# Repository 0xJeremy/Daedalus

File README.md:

# Daedalus Motor Controller

### Board Layout

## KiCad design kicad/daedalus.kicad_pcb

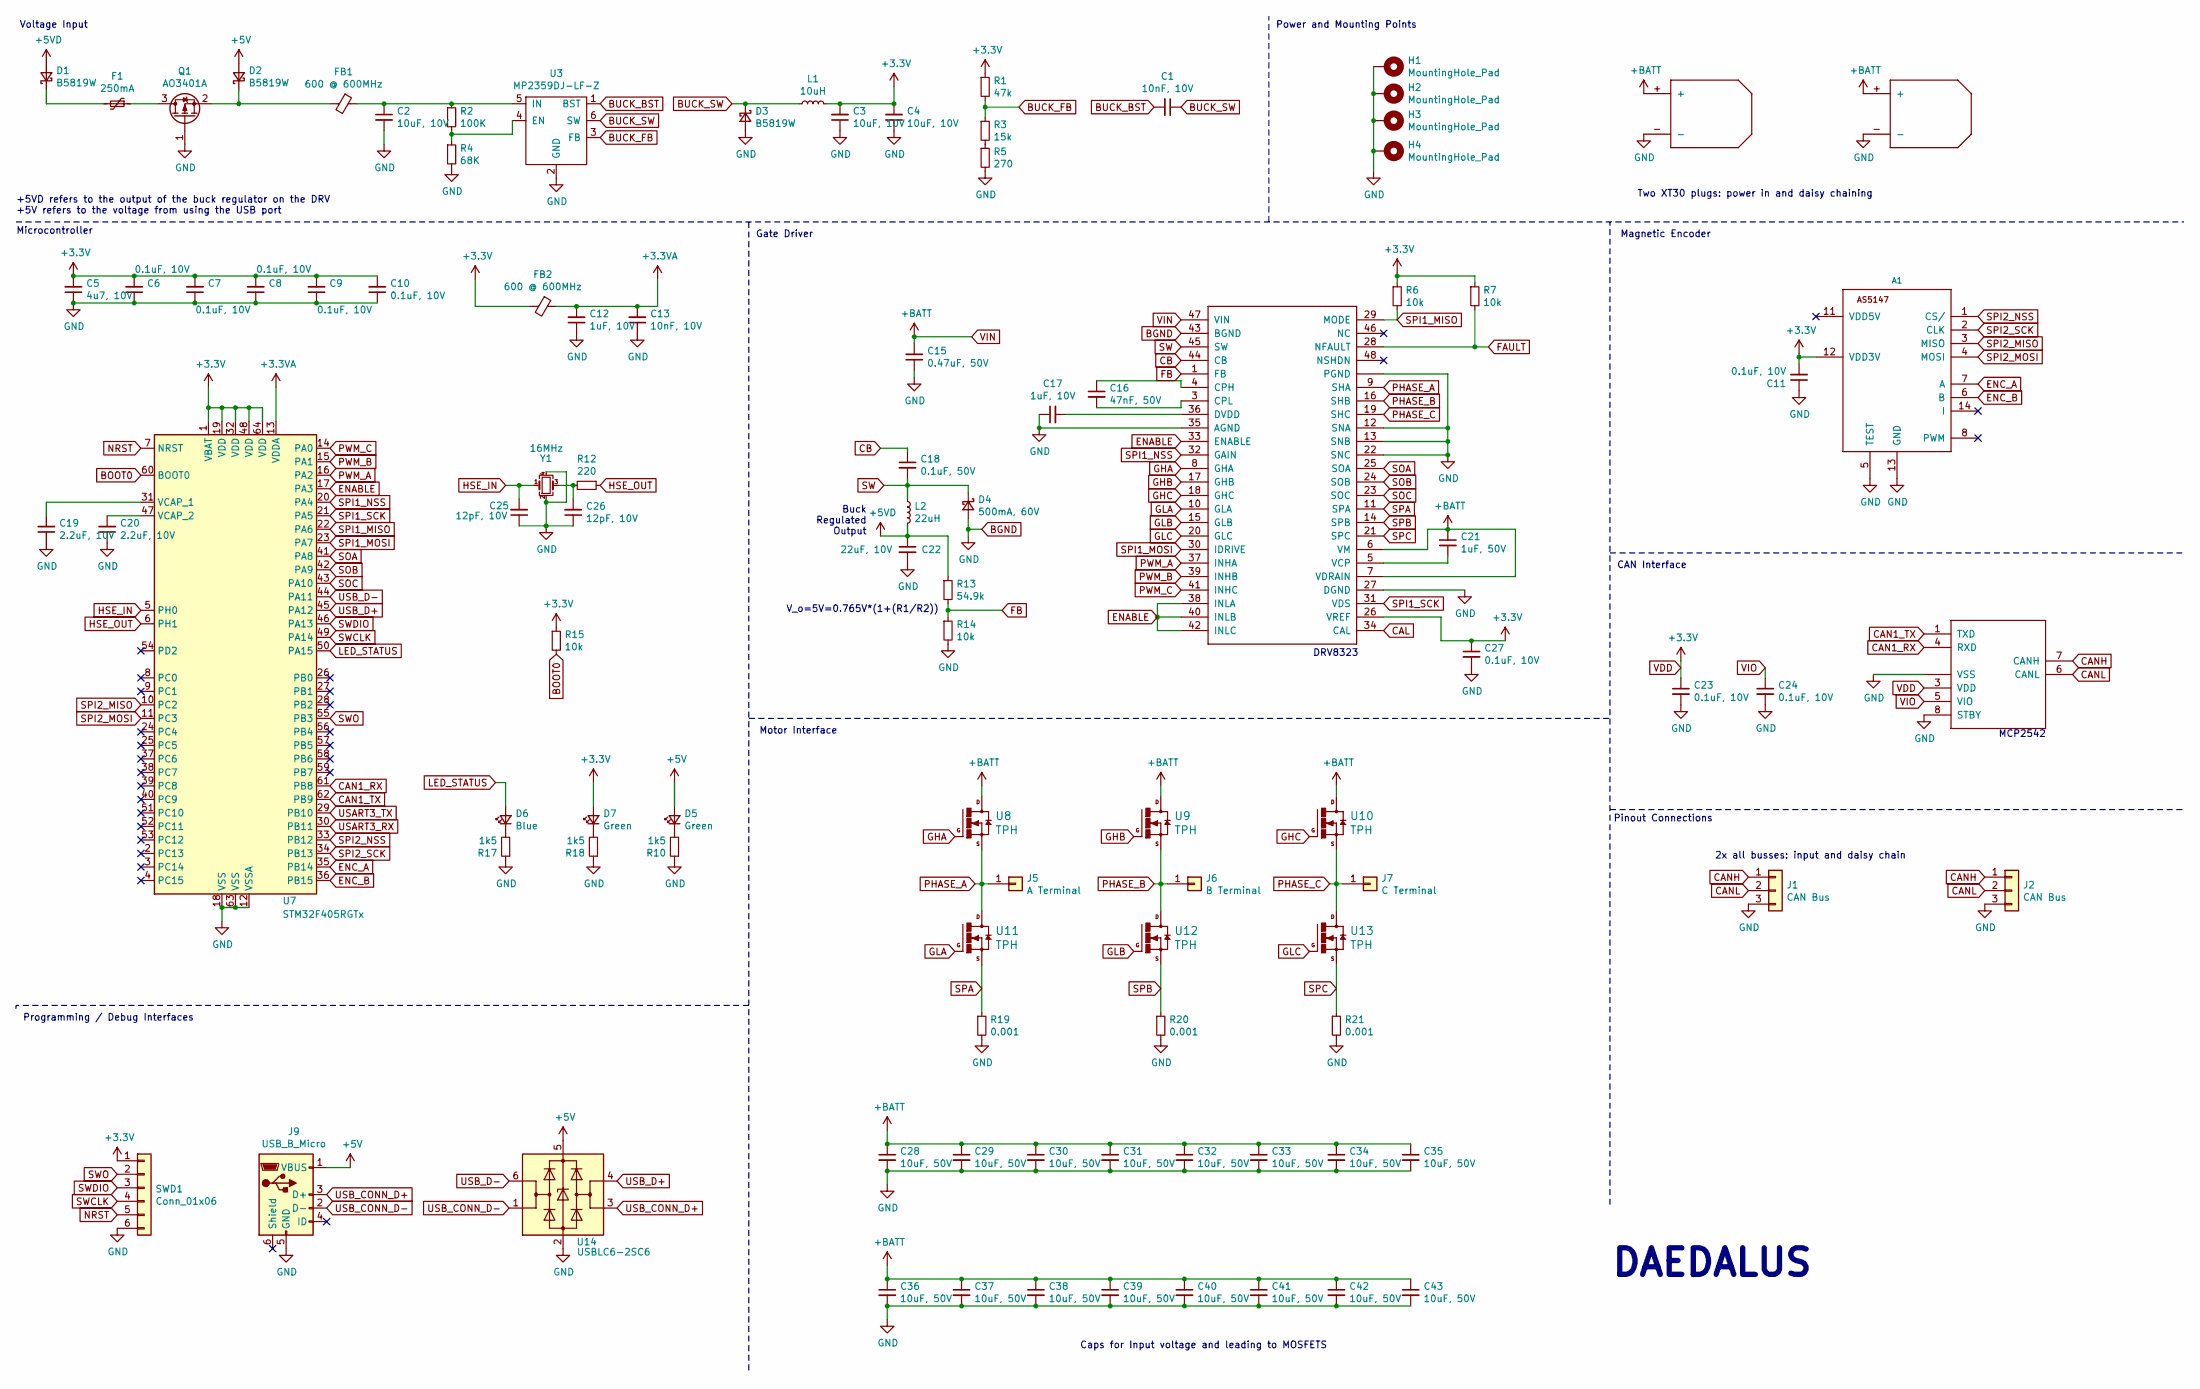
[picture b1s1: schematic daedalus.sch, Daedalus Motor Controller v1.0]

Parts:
A1: AS5147; TSSOP14_as5147
C1: 10nF, 10V; C_0402_1005Metric
C2, C3, C4: 10uF, 10V; C_0402_1005Metric
C5: 4u7, 10V; C_0402_1005Metric; LCSC Part # C23733
C6, C7, C8, C9, C10: 0.1uF, 10V; C_0402_1005Metric; LCSC Part # C1525
C11, C23, C24, C27: 0.1uF, 10V; C_0402_1005Metric
C12: 1uF, 10V; C_0402_1005Metric; LCSC Part # C1525
C13: 10nF, 10V; C_0402_1005Metric; LCSC Part # C1523
C15: 0.47uF, 50V; C_0402_1005Metric
C16: 47nF, 50V; C_0402_1005Metric
C17: 1uF, 10V; C_0402_1005Metric
C18: 0.1uF, 50V; C_0402_1005Metric
C19, C20: 2.2uF, 10V; C_0603_1608Metric; LCSC Part # C23630
C21: 1uF, 50V; C_0402_1005Metric
C22: 22uF, 10V; C_0402_1005Metric
C25, C26: 12pF, 10V; C_0402_1005Metric; LCSC Part # C1547
C28, C29, C30, C31, C32, C33, C34, C35, C36, C37, C38, C39, C40, C41, C42, C43: 10uF, 50V; C_0805_2012Metric
D1, D2, D3: B5819W; D_SOD-123
D4: 500mA, 60V; D_SOD-123
D5, D7: Green; LED_0603_1608Metric; LCSC Part # C2286
D6: Blue; LED_0603_1608Metric; LCSC Part # C2286
F1: 250mA; Fuse_0603_1608Metric
FB1: 600 @ 600MHz; L_0805_2012Metric
FB2: 600 @ 600MHz; L_0805_2012Metric; LCSC Part # C1015
H1, H2, H3, H4: MountingHole_Pad; MountingHole_2.7mm_M2.5_DIN965_Pad
J1, J2: CAN Bus; JST_PH_S3B-PH-SM4-TB_1x03-1MP_P2.00mm_Horizontal
J5: A Terminal; 18_AWG_PAD
J6: B Terminal; 18_AWG_PAD
J7: C Terminal; 18_AWG_PAD
J9: USB_B_Micro; USB_Micro-AB_Molex_47590-0001
L1: 10uH; L_0603_1608Metric
L2: 22uH; L_0603_1608Metric
Q1: AO3401A; SOT-23
R1: 47k; R_0402_1005Metric
R2: 100K; R_0402_1005Metric
R3: 15k; R_0402_1005Metric
R4: 68K; R_0402_1005Metric
R5: 270; R_0402_1005Metric
R6, R7, R14: 10k; R_0402_1005Metric
R10, R17, R18: 1k5; R_0402_1005Metric; LCSC Part # C25867
R12: 220; R_0402_1005Metric; LCSC Part # C22962
R13: 54.9k; R_0402_1005Metric
R15: 10k; R_0402_1005Metric; LCSC Part # C25744
R19, R20, R21: 0.001; R_1206_3216Metric
SWD1: Conn_01x06; JST_PH_S6B-PH-K_1x06_P2.00mm_Horizontal
U1, U2: XT30; XT30_HORIZONTAL
U3: MP2359DJ-LF-Z; SOT-23-6
U5: DRV8323RH; QFN50P700X700X90-49N
U6: MCP2542; TDFN
U7: STM32F405RGTx; LQFP-64_10x10mm_P0.5mm; LCSC Part # C15742
U8, U9, U10, U11, U12, U13: TPH; TRANS_TPH5900CNH,L1Q
U14: USBLC6-2SC6; SOT-23-6
Y1: 16MHz; Crystal_SMD_3225-4Pin_3.2x2.5mm; LCSC Part # C13738

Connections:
+3.3VA: C12.2, C13.2, FB2.1, U7.13 (VDDA)
+5V: D2.2 (A), D5.2 (A), J9.1 (VBUS), U14.5 (VBUS)
+5VD: C22.1, D1.2 (A), L2.2, R13.1
BGND: A1.5 (TEST), A1.13 (GND), C2.2, C3.1, C4.1, C5.1, C6.1, C7.1, C8.1, C9.1, C10.1, C11.1, C12.1, C13.1, C15.1, C17.1, C19.1, C20.1, C22.2, C23.2, C24.2, C25.1, C26.1, C27.2, C28.2, C29.2, C30.2, C31.2, C32.2, C33.2, C34.2, C35.2, C36.2, C37.2, C38.2, C39.2, C40.2, C41.2, C42.2, C43.2, D3.2 (A), D4.2 (A), H1.1, H2.1, H3.1, H4.1, J1.3, J2.3, J9.5 (GND), Q1.1 (G), R4.2, R5.2, R10.1, R14.2, R17.1, R18.1, R19.2, R20.2, R21.2, SWD1.6, U1.-, U2.-, U3.2 (GND), U5.2 (PGND), U5.12 (SNA), U5.13 (SNB), U5.22 (SNC), U5.27 (DGND), U5.35 (AGND), U5.43 (BGND), U5.49 (PGND), U6.2 (VSS), U6.8 (STBY), U6.9 (VSS), U7.12 (VSSA), U7.18 (VSS), U7.63 (VSS), U14.2 (GND), Y1.2, Y1.4
BOOT0: R15.2, U7.60 (BOOT0)
BUCK_BST: C1.2, U3.1 (BST)
BUCK_FB: R1.2, R3.1, U3.3 (FB)
BUCK_SW: C1.1, D3.1 (K), L1.1, U3.6 (SW)
CAL: U5.34 (CAL)
CAN1_RX: U6.4 (RXD), U7.61 (PB8)
CAN1_TX: U6.1 (TXD), U7.62 (PB9)
CANH: J1.1, J2.1, U6.7 (CANH)
CANL: J1.2, J2.2, U6.6 (CANL)
CB: C18.1, U5.44 (CB)
ENABLE: U5.33 (ENABLE), U5.38 (INLA), U5.40 (INLB), U5.42 (INLC), U7.17 (PA3)
ENC_A: A1.7 (A), U7.35 (PB14)
ENC_B: A1.6 (B), U7.36 (PB15)
FAULT: R7.2, U5.28 (NFAULT)
FB: R13.2, R14.1, U5.1 (FB)
GHA: U5.8 (GHA), U8.4 (G)
GHB: U5.17 (GHB), U9.4 (G)
GHC: U5.18 (GHC), U10.4 (G)
GLA: U5.10 (GLA), U11.4 (G)
GLB: U5.15 (GLB), U12.4 (G)
GLC: U5.20 (GLC), U13.4 (G)
HSE_IN: C25.2, U7.5 (PH0), Y1.1
HSE_OUT: R12.1, U7.6 (PH1)
LED_STATUS: D6.2 (A), U7.50 (PA15)
NRST: SWD1.5, U7.7 (NRST)
unnamed: C2.1, FB1.1, R2.1, U3.5 (IN)
unnamed: C16.1, U5.4 (CPH)
unnamed: C16.2, U5.3 (CPL)
unnamed: C17.2, U5.36 (DVDD)
unnamed: C19.2, U7.31 (VCAP_1)
unnamed: C20.2, U7.47 (VCAP_2)
unnamed: C21.2, U5.5 (VCP)
unnamed: C26.2, R12.2, Y1.3
unnamed: D1.1 (K), F1.2
unnamed: D2.1 (K), FB1.2, Q1.2 (S)
unnamed: D5.1 (K), R10.2
unnamed: D6.1 (K), R17.2
unnamed: D7.1 (K), R18.2
unnamed: F1.1, Q1.3 (D)
unnamed: R2.2, R4.1, U3.4 (EN)
unnamed: R3.2, R5.1
PHASE_A: J5.1, U5.9 (SHA), U8.1 (S), U8.2 (S), U8.3 (S), U11.5 (D), U11.6 (D), U11.7 (D), U11.8 (D), U11.EP (D)
PHASE_B: J6.1, U5.16 (SHB), U9.1 (S), U9.2 (S), U9.3 (S), U12.5 (D), U12.6 (D), U12.7 (D), U12.8 (D), U12.EP (D)
PHASE_C: J7.1, U5.19 (SHC), U10.1 (S), U10.2 (S), U10.3 (S), U13.5 (D), U13.6 (D), U13.7 (D), U13.8 (D), U13.EP (D)
PWM_A: U5.37 (INHA), U7.16 (PA2)
PWM_B: U5.39 (INHB), U7.15 (PA1)
PWM_C: U5.41 (INHC), U7.14 (PA0)
SOA: U5.25 (SOA), U7.41 (PA8)
SOB: U5.24 (SOB), U7.42 (PA9)
SOC: U5.23 (SOC), U7.43 (PA10)
SPA: R19.1, U5.11 (SPA), U11.1 (S), U11.2 (S), U11.3 (S)
SPB: R20.1, U5.14 (SPB), U12.1 (S), U12.2 (S), U12.3 (S)
SPC: R21.1, U5.21 (SPC), U13.1 (S), U13.2 (S), U13.3 (S)
SPI1_MISO: R6.2, U5.29 (MODE), U7.22 (PA6)
SPI1_MOSI: U5.30 (IDRIVE), U7.23 (PA7)
SPI1_NSS: U5.32 (GAIN), U7.20 (PA4)
SPI1_SCK: U5.31 (VDS), U7.21 (PA5)
SPI2_MISO: A1.3 (MISO), U7.10 (PC2)
SPI2_MOSI: A1.4 (MOSI), U7.11 (PC3)
SPI2_NSS: A1.1 (CS/), U7.33 (PB12)
SPI2_SCK: A1.2 (CLK), U7.34 (PB13)
SW: C18.2, D4.1 (K), L2.1, U5.45 (SW)
SWCLK: SWD1.4, U7.49 (PA14)
SWDIO: SWD1.3, U7.46 (PA13)
SWO: SWD1.2, U7.55 (PB3)
USART3_RX: U7.30 (PB11)
USART3_TX: U7.29 (PB10)
USB_CONN_D+: J9.3 (D+), U14.3 (I/O2)
USB_CONN_D-: J9.2 (D-), U14.1 (I/O1)
USB_D+: U7.45 (PA12), U14.4 (I/O2)
USB_D-: U7.44 (PA11), U14.6 (I/O1)
VDD: A1.12 (VDD3V), C3.2, C4.2, C5.2, C6.2, C7.2, C8.2, C9.2, C10.2, C11.2, C23.1, C27.1, D7.2 (A), FB2.2, L1.2, R1.1, R6.1, R7.1, R15.1, SWD1.1, U5.26 (VREF), U6.3 (VDD), U7.1 (VBAT), U7.19 (VDD), U7.32 (VDD), U7.48 (VDD), U7.64 (VDD)
VIN: C15.2, C21.1, C28.1, C29.1, C30.1, C31.1, C32.1, C33.1, C34.1, C35.1, C36.1, C37.1, C38.1, C39.1, C40.1, C41.1, C42.1, C43.1, U1.+, U2.+, U5.6 (VM), U5.7 (VDRAIN), U5.47 (VIN), U8.5 (D), U8.6 (D), U8.7 (D), U8.8 (D), U8.EP (D), U9.5 (D), U9.6 (D), U9.7 (D), U9.8 (D), U9.EP (D), U10.5 (D), U10.6 (D), U10.7 (D), U10.8 (D), U10.EP (D)
VIO: C24.1, U6.5 (VIO)

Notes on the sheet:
Microcontroller
Voltage Input
Programming / Debug Interfaces
Power and Mounting Points
Gate Driver
Magnetic Encoder
DRV8323
Motor Interface
CAN Interface
MCP2542
Pinout Connections
V_o=5V=0.765V*(1+(R1/R2))
Buck Regulated Output
+5VD refers to the output of the buck regulator on the DRV +5V refers to the voltage from using the USB port
Two XT30 plugs: power in and daisy chaining
2x all busses: input and daisy chain
Caps for Input voltage and leading to MOSFETS
DAEDALUS

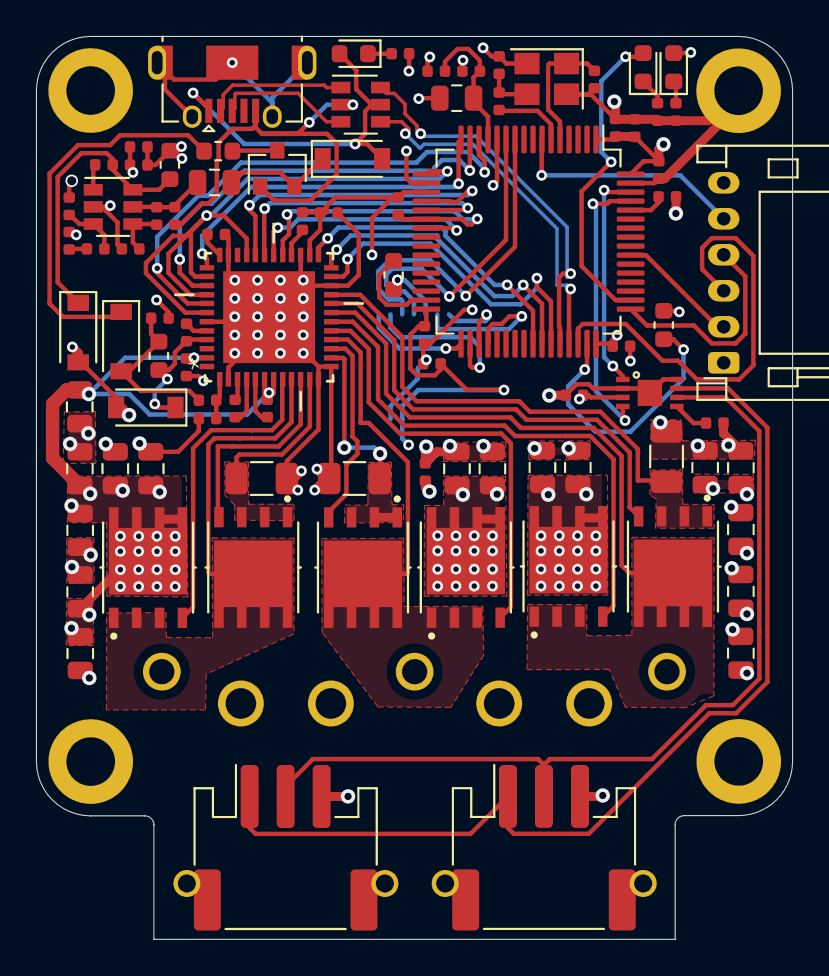
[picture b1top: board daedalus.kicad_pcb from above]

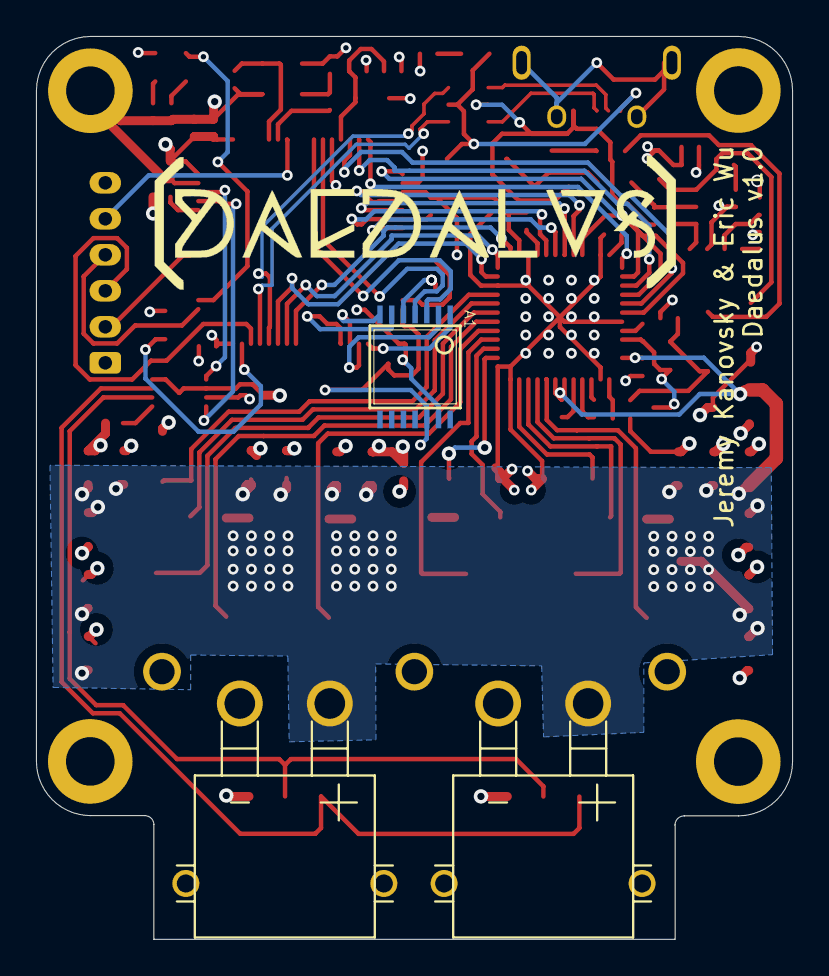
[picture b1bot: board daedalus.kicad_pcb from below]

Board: 4 copper layers, 42.0 x 50.2 mm, 98 parts (3 on the bottom side), 75 nets.

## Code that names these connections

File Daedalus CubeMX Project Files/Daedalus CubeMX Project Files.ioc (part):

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PC3.Mode=Full_Duplex_Master
PA6.Mode=Full_Duplex_Master
PH0-OSC_IN.Signal=RCC_OSC_IN
Mcu.UserName=STM32F405RGTx
PB10.Mode=Asynchronous
PA11.Mode=Device_Only
PB11.Signal=USART3_RX
PB13.Signal=SPI2_SCK
PA12.Signal=USB_OTG_FS_DP
PA4.Mode=NSS_Signal_Hard_Input
PB6.Signal=I2C1_SCL
PB6.Mode=I2C
PC3.Signal=SPI2_MOSI
PH0-OSC_IN.Mode=HSE-External-Oscillator
RCC.HSE_VALUE=25000000
PB3.Mode=Trace_Asynchronous_SW
PA14.Mode=Trace_Asynchronous_SW
PB7.Signal=I2C1_SDA
PH1-OSC_OUT.Mode=HSE-External-Oscillator
Mcu.Package=LQFP64
PB9.Signal=CAN1_TX
PA6.Signal=SPI1_MISO
PB12.Mode=NSS_Signal_Hard_Output
PA15.Signal=GPIO_Output
PB13.Mode=Full_Duplex_Master
PB4.Signal=GPIO_Output
PA5.Mode=Full_Duplex_Master
PA7.Mode=Full_Duplex_Master
PC2.Signal=SPI2_MISO
PC2.Mode=Full_Duplex_Master
PA0-WKUP.Signal=GPIO_Output
PA13.Signal=SYS_JTMS-SWDIO
PB11.Mode=Asynchronous
PB9.Mode=CAN_Activate
PA1.Signal=GPIO_Output
PB10.Signal=USART3_TX
PA5.Signal=SPI1_SCK
board=custom
PH1-OSC_OUT.Signal=RCC_OSC_OUT
PA13.Mode=Trace_Asynchronous_SW
Mcu.Name=STM32F405RGTx
PA2.Signal=GPIO_Output
PB3.Signal=SYS_JTDO-SWO
PA4.Signal=SPI1_NSS
RCC.SYSCLKFreq_VALUE=16000000
PA12.Mode=Device_Only
PB7.Mode=I2C
PA11.Signal=USB_OTG_FS_DM
PA14.Signal=SYS_JTCK-SWCLK
PB8.Mode=CAN_Activate
PB8.Signal=CAN1_RX
PB0.Signal=GPIO_Output
PB12.Signal=SPI2_NSS
PA7.Signal=SPI1_MOSI

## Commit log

2021-02-13 Added initial schematic
2021-02-13 Updated schematic with MPU6050
2021-02-14 Added footprints and side headers
2021-02-22 Began work adding DRV8323
2021-02-22 Added SPI busses, updated CubeMX files
2021-02-23 Added CAN interface, fixed value labels
2021-02-23 Updated buck regulator output, removed battery connector
2021-02-24 Updated schematic, added footprints, added BOM
2021-02-24 Began board layout
2021-02-25 Began sample routing, removed boot switch
2021-02-25 Updated footprint and routing
2021-02-28 Updated schematic, began v3 layout
2021-02-28 Finished rough layout v3
2021-02-28 Added 5V LED, finished standard routes; about to start pours
2021-02-28 Finished v3 board layout; needs fill cleanup
2021-03-01 Fixed design rules, fixed pours
2021-03-02 updated step files
2021-03-02 fixing xt30
2021-03-02 Added board renders, updated board schematic
2021-03-02 Added initial BOM
2021-03-02 Added new logo and render
2021-03-02 Finished preliminary BOM
2021-03-04 Updated vias, added vias, removed i2c line and pullups, added renders
2021-03-04 Updated file structure, added new BOM
2021-03-04 Removed outdated files
2021-03-04 Fixed README
2021-03-04 Added BOM
2021-03-04 Added PCBWay Pitch
2021-03-04 Updated logo with render, added silkscreen bmp
2021-03-04 Update Pitch.md
    OrbitActuator -> OrbitDrive :)
2021-03-04 Updated README logo
2021-03-05 Added gerber files and centroid file
2021-03-08 Updated gerber file for manufacturing
2021-05-07 Added images
2021-06-15 Added .step model
2021-06-15 Added test stand model
